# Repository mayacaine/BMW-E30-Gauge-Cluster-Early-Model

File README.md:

# BMW E30 Gauge Cluster Early Model
The goal for this project is to reverse engineer every PCB in the gauge cluster for early model year BMW E30's. This includes the main PCB referred to as the "Nexus" board and the smaller boards that are part of the tachometer and speedometer gauge assemblies. The SI (Service Interval) board has already been successfully reverse engineered and improved by Fabian Gmeiner. His project is linked below. 

## Fabian Gmeiner's SI board project:
https://github.com/FabianGmeiner/BMW_E30_SI_Board

# Late Model Clusters:
If you have a late model cluster and need parts for that, check out the progress of the late model project here: https://github.com/Ansel84/BMW-E30-Gauge-Cluster-Late-Model

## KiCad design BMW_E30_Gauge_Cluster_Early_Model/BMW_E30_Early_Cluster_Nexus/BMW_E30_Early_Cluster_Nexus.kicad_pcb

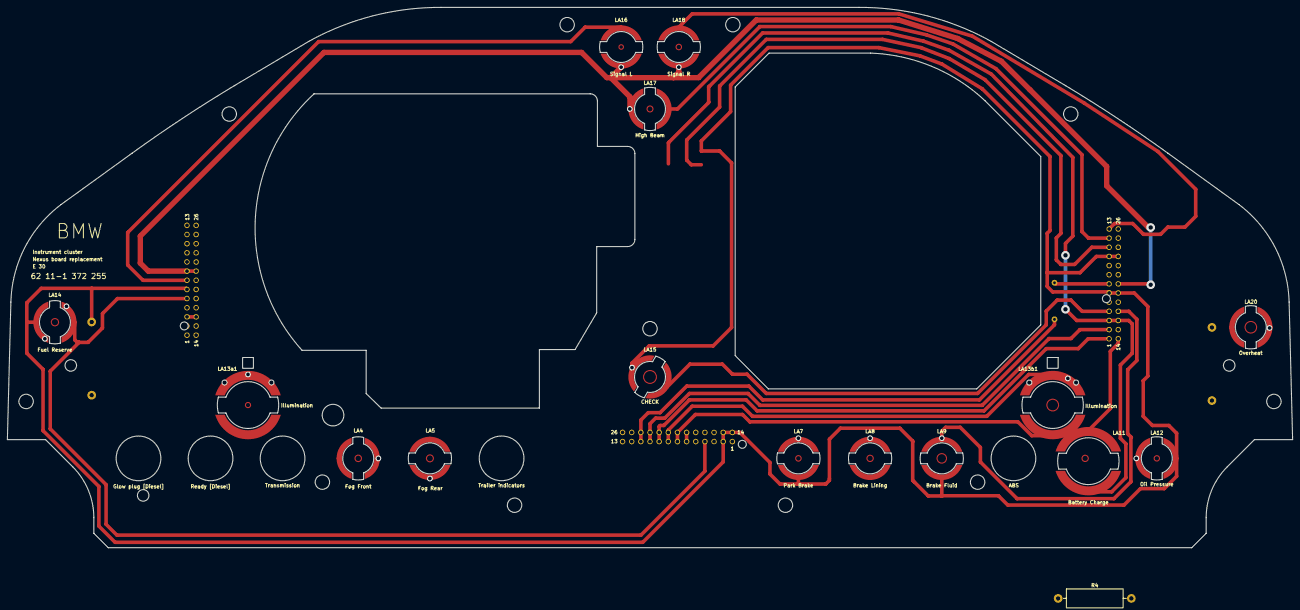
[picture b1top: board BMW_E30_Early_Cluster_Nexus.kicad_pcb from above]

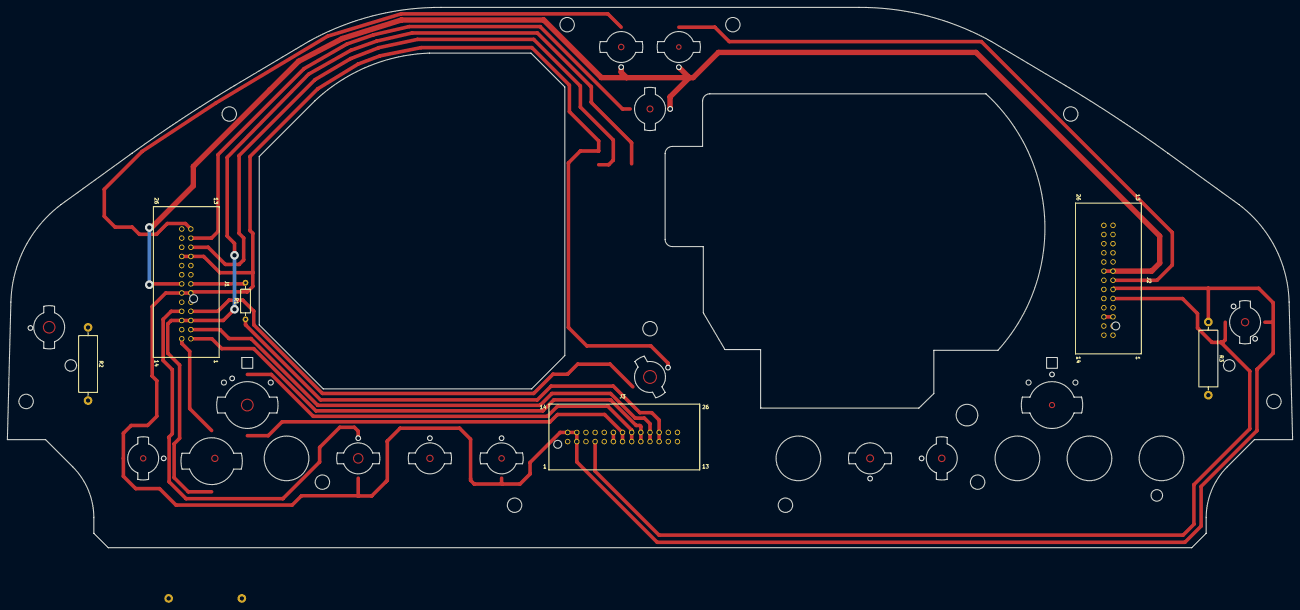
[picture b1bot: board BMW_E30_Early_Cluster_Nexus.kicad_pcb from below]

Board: 2 copper layers, 356.8 x 150.0 mm, 22 parts (6 on the bottom side), 24 nets.

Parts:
J1: C1 - Blue Connector; TE_827881-3
J2: C2 - White Connector; TE_827881-2
J3: C3 - Yellow Connector; TE_827881-1
LA4: Fog Front; 2721MF
LA5: Fog Rear; 2721MF
LA7: Park Brake; 2721MF
LA8: Brake Lining; 2721MF
LA9: Brake Fluid; 2721MF
LA11: Battery Charge; 2821MF
LA12: Oil Pressure; 2721MF
LA13a1, LA13b1: Illumination; 2821MF
LA14: Fuel Reserve; 2721MF
LA15: CHECK; 2721MF
LA16: Signal L; 2721MF
LA17: High Beam; 2721MF
LA18: Signal R; 2721MF
LA20: Overheat; 2721MF
R1: 16k; R_Axial_DIN0207_L6.3mm_D2.5mm_P10.16mm_Horizontal
R2, R3: 68R; R_Axial_DIN0516_L15.5mm_D5.0mm_P20.32mm_Horizontal
R4: 51R; R_Axial_DIN0516_L15.5mm_D5.0mm_P20.32mm_Horizontal

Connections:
+12 T15: J1.6, J1.10, J1.19, J1.23, J2.6, J3.2, J3.14, J3.15, LA7.2 (+), LA9.2 (+), LA12.2 (+), LA14.1 (-), LA15.1 (-), LA20.1 (-), R2.1, R3.1
+12 T15_ACC: J2.13, J3.13
+12 T30: J1.2, J3.10, J3.23
Brake_fluid_ind-: J1.17, LA9.1 (-)
Charge_Ind+: J1.14, LA11.1 (-), R4.1
Charge_ind-: J1.3, J1.16, LA11.2 (+), R4.2
Check_Control_ind: J1.4, LA15.2 (+)
Engine_spd_input: J3.11, J3.24, R1.1
Fog_ind+: J2.22, LA4.1 (-)
Fuel_level: J2.4, J3.5
Fuel_rate_input: J1.11, J3.25
GNDPWR: J1.20, J2.3, J2.8, J2.16, J2.21, J3.1, LA4.2 (+), LA5.1 (-), LA8.1 (-), LA16.2 (+), LA17.1 (-), LA18.2 (+)
High_beam_ind: J1.12, LA17.2 (+)
Illum+: J2.24, J3.8, J3.21, LA13a1.1 (-), LA13b1.1 (-)
Illum-: J2.23, J3.7, J3.20, LA13a1.2 (+), LA13b1.2 (+)
LH_ind: J2.7, LA16.1 (-)
Low_Fuel_ind-: J2.5, J3.4, LA14.2 (+)
Oil_pressure_ind-: J1.18, LA12.1 (-)
Overheat_ind-: J1.25, LA20.2 (+)
Park_brake_ind-: J2.1, J3.6, J3.19, LA7.1 (-)
RAW_RPM_input: J1.7, R1.2
RH_ind: J1.13, LA18.1 (-)
Rear_fog_ind+: J2.14, LA5.2 (+)
START: J1.1, J3.9, J3.22

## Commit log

2025-08-07 Adding KiCad project files
2025-08-07 Add .gitignore file
2025-08-07 Change folder name
    changed "pictures" folder to "resources"
2025-08-08 Layout Updates
    Layout traces completed. All footprints are also in now and lined up with the scan. Still need to fix illum and charge indicator conflict on the right side of the board.
2025-08-08 Generate board cut file
    for laser cutting a reference board
2025-08-09 Update gitignore file
2025-08-10 Layout Update
2025-08-11 Add Speedometer and Tach/EG projects
2025-08-11 Layout update
    Fixed overlapping pads between charge indicator lamp and left side illumination lamp pads.
2025-08-13 Layout Update
    Added in resistor parallel to the charge indicator light. This will prevent the alternator from not charging in the event that the charge indicator bulb burns out.
2025-08-13 Added test points for easy SI board delete.
2025-08-13 Added SI Bypass
    Added in jumper pads that allow the SI board to be fully removed while maintaining functionality of the temperature gauge which would otherwise be disconnected.
    Idea by user: mayacaine
    Edited and merged by: Ansel84
